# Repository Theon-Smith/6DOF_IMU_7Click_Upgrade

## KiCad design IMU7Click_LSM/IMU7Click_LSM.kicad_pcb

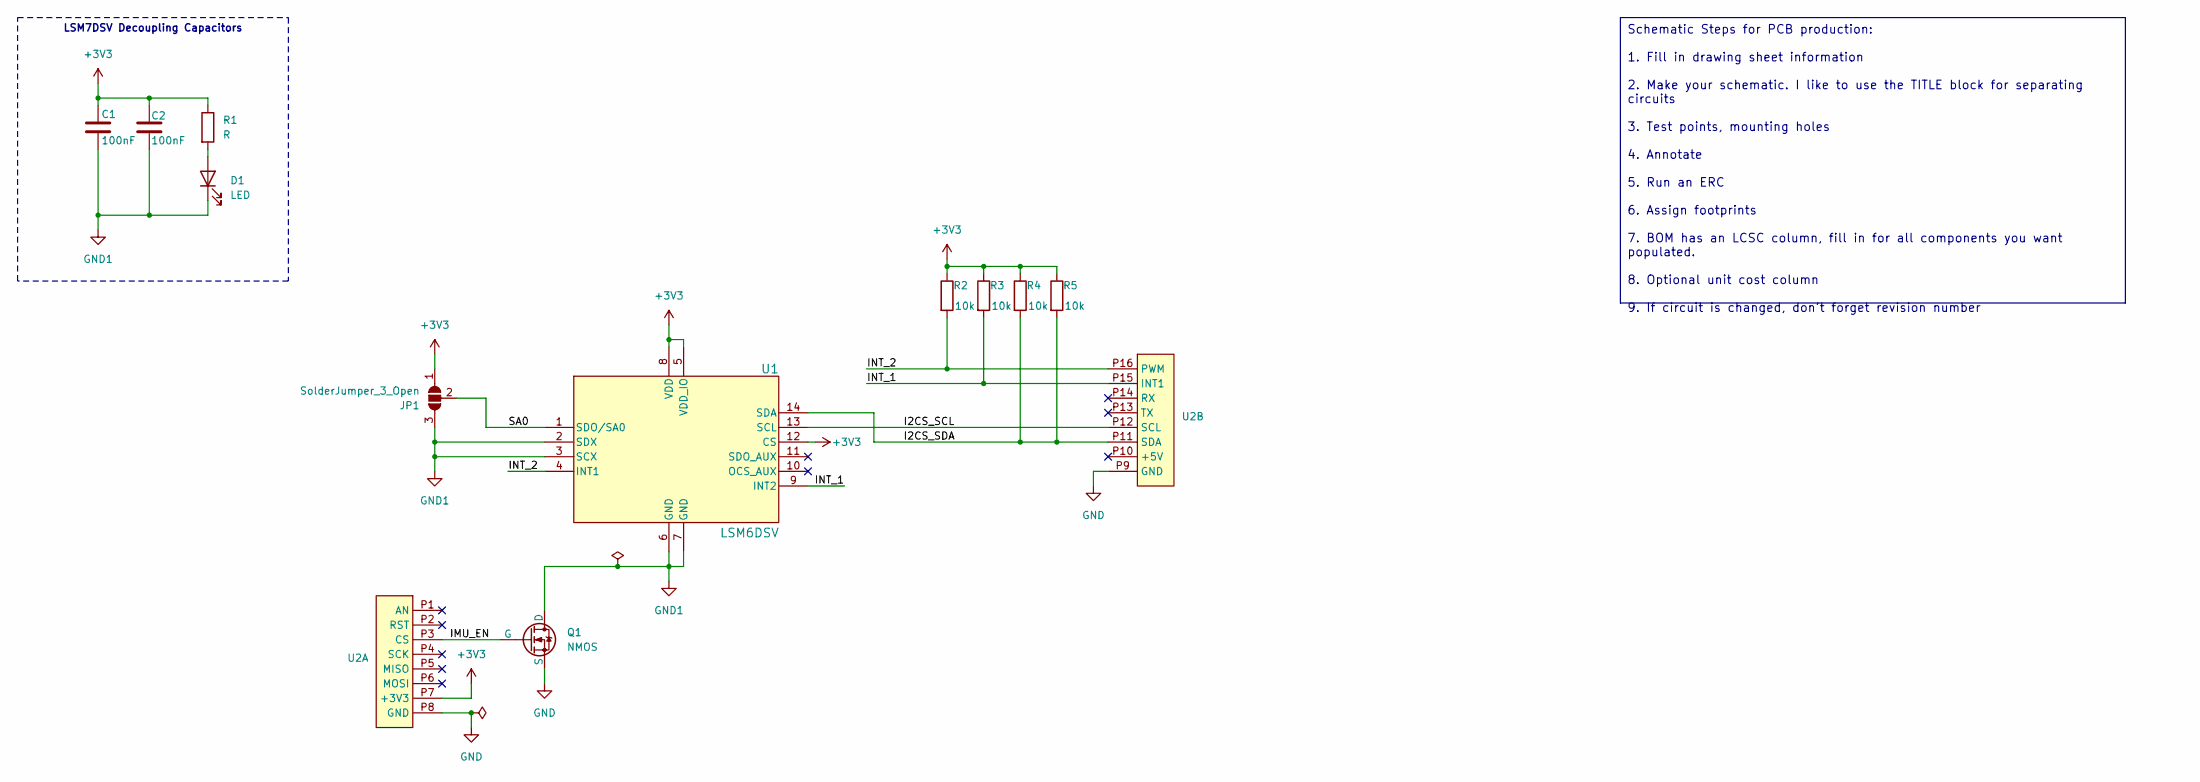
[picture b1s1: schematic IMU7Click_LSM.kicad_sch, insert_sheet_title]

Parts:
C1, C2: 100nF; C_0603_1608Metric_Pad1.08x0.95mm_HandSolder
D1: LED; LED_0805_2012Metric_Pad1.15x1.40mm_HandSolder
JP1: SolderJumper_3_Open; SolderJumper-3_P1.3mm_Open_RoundedPad1.0x1.5mm_NumberLabels
Q1: NMOS; SOT-23-3
R1: R; R_0603_1608Metric_Pad0.98x0.95mm_HandSolder
R2, R3, R4, R5: 10k; R_0603_1608Metric_Pad0.98x0.95mm_HandSolder
U1: LSM6DSV; LGA14-L_2P59X3P1X0P5_STM
U2: MIKROBUS_HOST_CONN

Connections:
+3V3: C1.1, C2.1, JP1.1 (A), R1.1, R2.1, R3.1, R4.1, R5.1, U1.5 (VDD_IO), U1.8 (VDD), U1.12 (CS), U2.P7 (+3V3)
/I2CS_SCL: U1.13 (SCL), U2.P12 (SCL)
/I2CS_SDA: R4.2, R5.2, U1.14 (SDA), U2.P11 (SDA)
/IMU_EN: Q1.2 (G), U2.P3 (CS)
/INT_1: R3.2, U1.9 (INT2), U2.P15 (INT1)
/INT_2: R2.2, U1.4 (INT1), U2.P16 (PWM)
/SA0: JP1.2 (C), U1.1 (SDO/SA0)
GND: Q1.3 (S), U2.P8 (GND), U2.P9 (GND)
GND1: C1.2, C2.2, D1.1 (K), JP1.3 (B), Q1.1 (D), U1.2 (SDX), U1.3 (SCX), U1.6 (GND), U1.7 (GND)
unnamed: D1.2 (A), R1.2

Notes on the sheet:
LSM7DSV Decoupling Capacitors
Schematic Steps for PCB production: 1. Fill in drawing sheet information 2. Make your schematic. I like to use the TITLE block for separating circuits 3. Test points, mounting holes 4. Annotate 5. Run an ERC 6. Assign footprints 7. BOM has an LCSC column, fill in for all components you want populat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

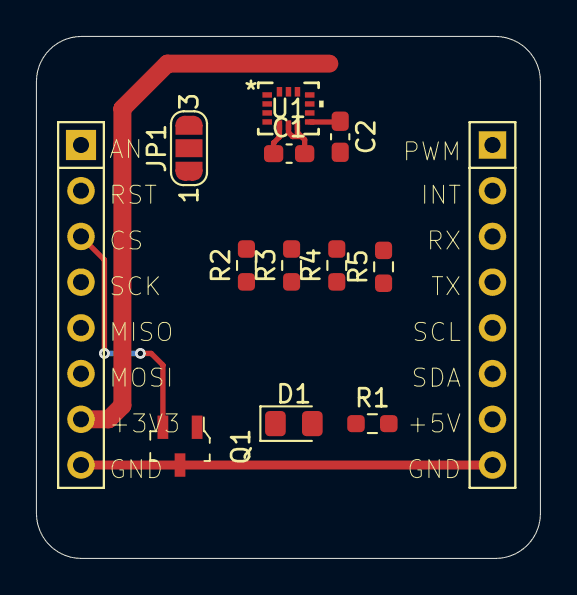
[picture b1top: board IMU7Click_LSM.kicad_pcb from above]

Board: 2 copper layers, 28.0 x 29.0 mm, 12 parts (0 on the bottom side), 10 nets.

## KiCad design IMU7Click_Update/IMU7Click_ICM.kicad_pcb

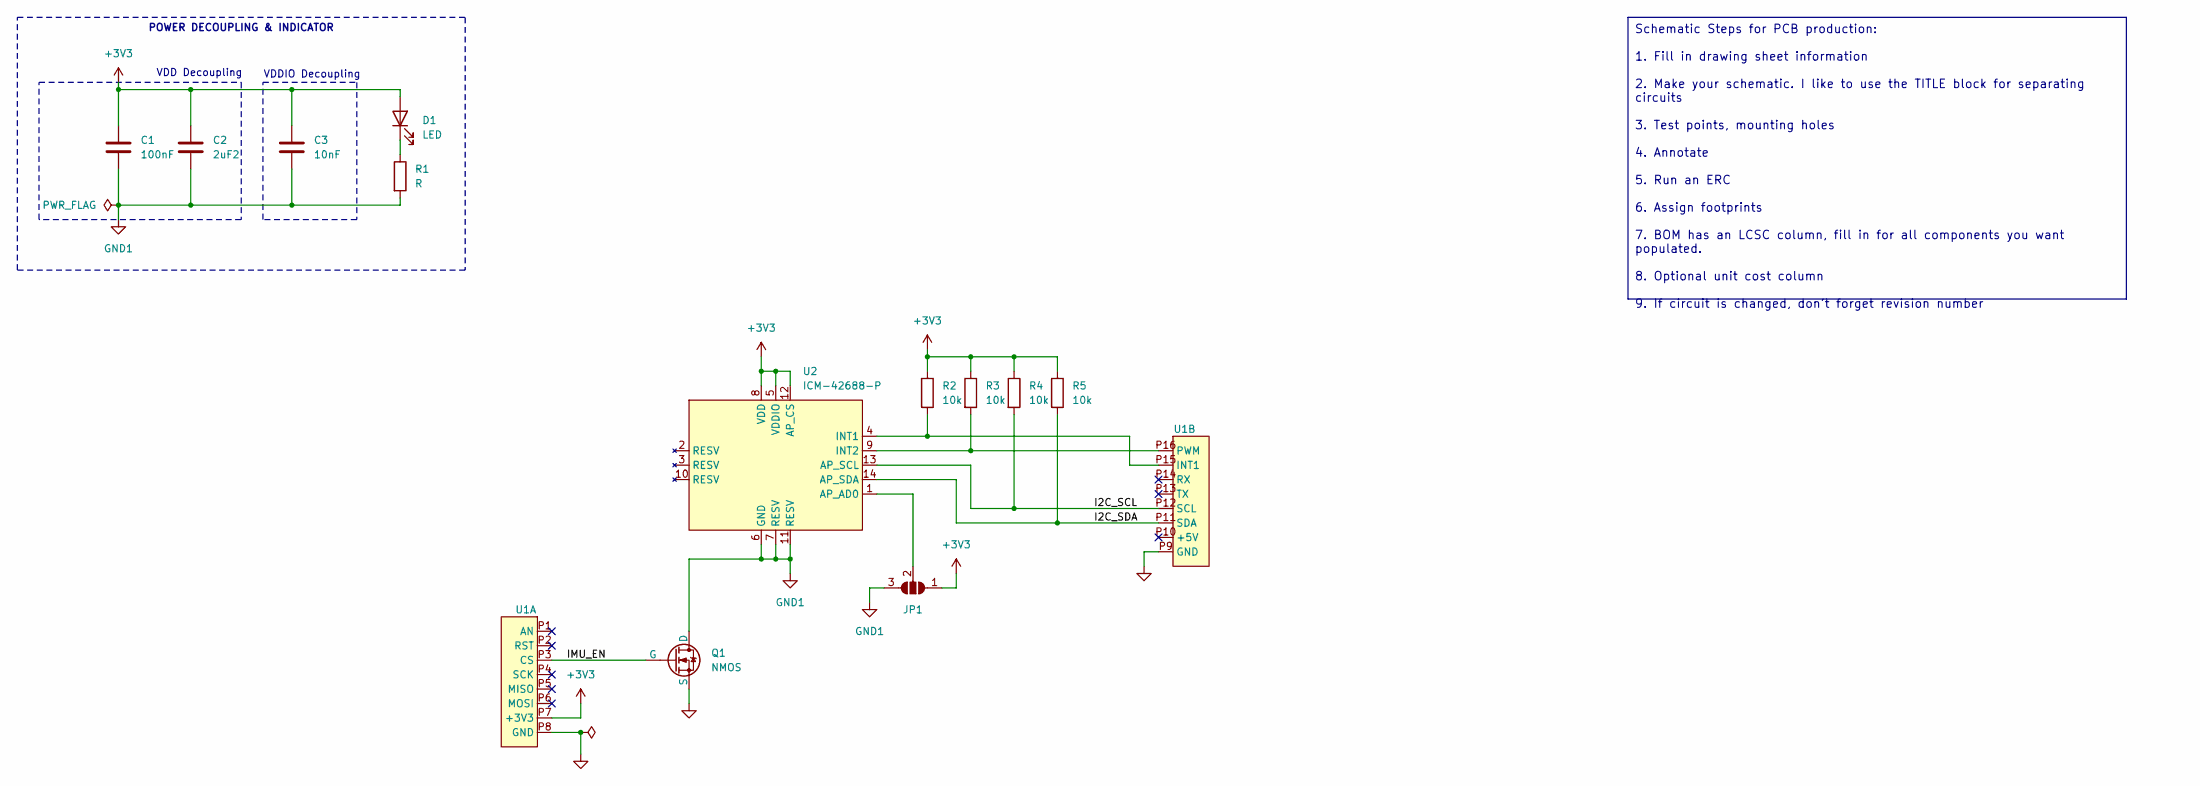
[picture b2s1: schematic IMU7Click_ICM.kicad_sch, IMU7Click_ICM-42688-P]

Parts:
C1: 100nF; C_0603_1608Metric_Pad1.08x0.95mm_HandSolder
C2: 2uF2; C_0603_1608Metric_Pad1.08x0.95mm_HandSolder
C3: 10nF; C_0603_1608Metric_Pad1.08x0.95mm_HandSolder
D1: LED; LED_0805_2012Metric_Pad1.15x1.40mm_HandSolder
JP1: SolderJumper_3_Open; SolderJumper-3_P1.3mm_Open_RoundedPad1.0x1.5mm_NumberLabels
Q1: NMOS; SOT-23-3
R1: R; R_0603_1608Metric_Pad0.98x0.95mm_HandSolder
R2, R3, R4, R5: 10k; R_0603_1608Metric_Pad0.98x0.95mm_HandSolder
U1: MIKROBUS_HOST_CONN
U2: ICM-42688-P

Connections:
+3V3: C1.1, C2.1, C3.1, D1.2 (A), JP1.1 (A), R2.1, R3.1, R4.1, R5.1, U1.P7 (+3V3), U2.5 (VDDIO), U2.8 (VDD), U2.12 (AP_CS)
/I2C_SCL: R4.2, U1.P12 (SCL), U2.13 (AP_SCL)
/I2C_SDA: R5.2, U1.P11 (SDA), U2.14 (AP_SDA)
/IMU_EN: Q1.2 (G), U1.P3 (CS)
GND: Q1.3 (S), U1.P8 (GND), U1.P9 (GND)
GND1: C1.2, C2.2, C3.2, JP1.3 (B), Q1.1 (D), R1.2, U2.6 (GND), U2.7 (RESV), U2.11 (RESV)
unnamed: D1.1 (K), R1.1
unnamed: JP1.2 (C), U2.1 (AP_AD0)
unnamed: R2.2, U1.P15 (INT1), U2.4 (INT1)
unnamed: R3.2, U1.P16 (PWM), U2.9 (INT2)

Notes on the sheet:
VDDIO Decoupling
VDD Decoupling
POWER DECOUPLING & INDICATOR
Schematic Steps for PCB production: 1. Fill in drawing sheet information 2. Make your schematic. I like to use the TITLE block for separating circuits 3. Test points, mounting holes 4. Annotate 5. Run an ERC 6. Assign footprints 7. BOM has an LCSC column, fill in for all components you want populat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

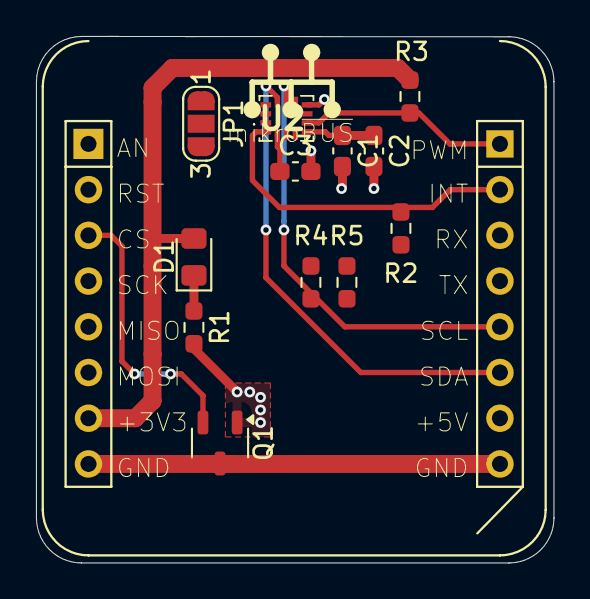
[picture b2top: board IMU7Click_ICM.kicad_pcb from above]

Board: 2 copper layers, 28.8 x 29.2 mm, 13 parts (0 on the bottom side), 10 nets.

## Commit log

2025-07-30 Whoops here is the stuff mentioned in the previous commit
2025-07-31 Started some tracing of routes. Had to add and remove everything because I fucked up
2025-08-01 started st imu board
